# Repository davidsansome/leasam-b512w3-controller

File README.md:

# Leasam B512W3 aircon wall controller — reverse engineering and replacement

This repo documents how a **Leasam Controls B512W3** wall pad talks to its outdoor relay module, and replaces it with an ESP32 board (controlled from Home Assistant) plus a repurposed Kindle as a touchscreen wall controller.

## Safety

> **⚠️ Use at your own risk.**
>
> - This project reverse-engineers and replaces part of the control electronics for a **mains-powered air conditioner / heat pump**. Getting it wrong can damage the unit, create a shock or fire hazard, or trip breakers in ways that aren't obvious from outside.
> - None of this is reviewed, endorsed, or supported by Leasam, your HVAC manufacturer, or your installer. It is **not a certified replacement part**.
> - It may **void your warranty**, your insurance, or breach local electrical regulations in your area — check before you start.
> - If you are not confident working inside a powered appliance, get a licensed electrician or HVAC technician to help, or to review your wiring before you connect anything.
> - Every measurement, assumption and bit of "guesswork" in these notes was true for **one specific unit**. Other Leasam models, firmware revisions, or installations may differ in ways that aren't safe to assume away.
> - **Never connect a prototype or replacement board and the original pad to the module at the same time.** Turn the aircon off at the isolator before changing any wiring.

## What's here

| | |
|---|---|
| [`leasam-b512w3-notes.md`](leasam-b512w3-notes.md) | Reverse-engineering notes on the original wall pad: how it talks to the outdoor relay module (protocol, timing, voltages), what's verified vs. guessed, and open questions. Start here. |
| [`pcb-images/`](pcb-images/) | Photos of the original pad's board, used for tracing the circuit. |
| [`scope-screenshots/`](scope-screenshots/) | Oscilloscope captures of the pad's signal, for each mode and fan speed. |
| [`replacement-board/`](replacement-board/) | The replacement: an ESP32 board that drives the relay module the way the original pad did (plus a thermostat), a second board that trickle-charges a tablet over the old in-wall cable, their firmware, and the KiCad designs. |
| [`kindle-controller/`](kindle-controller/) | A jailbroken Kindle Paperwhite, running a Rust e-ink UI, as the wall-mounted touchscreen — talking to Home Assistant, not to the relay module directly. Includes a 3D-printable wall case. |

## Suggested reading order

1. [`leasam-b512w3-notes.md`](leasam-b512w3-notes.md) — what the original pad does and how it was figured out.
2. [`replacement-board/README.md`](replacement-board/README.md) — the replacement electronics and firmware that take over that job.
3. [`replacement-board/breadboard-prototype.md`](replacement-board/breadboard-prototype.md) — a bring-up/test build using only easy-to-source parts, before committing to the PCB.
4. [`kindle-controller/README.md`](kindle-controller/README.md) — the wall-mounted touch UI.

## License

See [LICENSE](LICENSE).

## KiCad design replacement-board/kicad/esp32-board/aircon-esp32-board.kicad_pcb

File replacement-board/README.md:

# ESP32 aircon controller + tablet charger

> **⚠️ Use at your own risk.** These boards replace part of the control electronics for a mains-powered ducted air conditioner / heat pump, and connect directly to the relay module's wiring. Getting it wrong can damage the unit, create a shock or fire hazard, or void your warranty and insurance. See the [top-level README](../README.md#safety) for the full disclaimer.

Two boards replace the Leasam B512W3 wall pad:

1. **ESP32 board**, mounted near the relay module. It connects to the module's **POWER, COMMON, AUX** wires, sends the relay frames the original pad sent, and takes commands over Wi-Fi. It also feeds a switched, current-limited ~16 V output up the old in-wall cable.
2. **Tablet board**, behind the tablet at the other end of that cable. It steps the voltage down to 5 V on a current-limited USB-A socket for slow-charging an Android tablet.

| Files | |
|---|---|
| `firmware/aircon_controller/aircon_controller.ino` | ESP32 firmware, for both this board and the breadboard prototype |
| `firmware/aircon_controller/thermostat.h`, `firmware/thermostat_test/` | the thermostat's decisions, and host-side checks for them |
| `home-assistant/blueprints/aircon_rooms.yaml` | HA blueprint that gives the thermostat its rooms and their temperatures |
| `home-assistant/blueprints/tablet_charging.yaml` | HA blueprint that switches the tablet output on/off between battery thresholds |
| `kicad/esp32-board/` | KiCad project, designator map and netlist for board 1 |
| `kicad/tablet-board/` | KiCad project, designator map and netlist for board 2 |
| `case/` | 3D-printable case for board 1 |
| `../leasam-b512w3-notes.md` | reverse-engineering notes |
| `breadboard-prototype.md`, `kicad/breadboard-stage1/`, `kicad/breadboard-stage2/` | breadboard test circuit, built from common parts, for checking the module accepts our frames before fabricating |

See [`CHANGES.md`](CHANGES.md) for what changed after the 2026-11-04 design review, and why.

---

## 0. Power budget (measured)

| Measurement | Value |
|---|---|
| POWER open-circuit voltage | 19.0 V |
| Source resistance (load test: 1 kΩ / 470 Ω / 100 Ω → 18.50 / 18.11 / 15.80 V) | ≈ 20 Ω (≈ 25 Ω at light load) |
| Original pad's draw | 72 mA off, 90–100 mA running |

The design stays inside what the original pad drew:

| | Limit | Typical |
|---|---|---|
| Total draw from POWER (input limiter) | ≈ 105 mA | ~85–90 mA |
| ESP32 itself | — | ~10 mA average at ~16 V (Wi-Fi bursts come from the reservoir) |
| Tablet cable output (limiter 2) | ≈ 87 mA (80–93 mA) | ≤ ~64 mA worst case |
| Tablet USB output | ≈ 123 mA typ. at 5.07 V (R_ILIM 220k) | **≈ 0.5–0.75 W into the tablet** |

That's enough to charge a mostly-sleeping tablet slowly, and to support roughly **2 hours of screen-on time per day** on average.

The TPS2553 on the tablet board is the limit that matters in normal running. Limiter 2 sits well above the tablet board's worst-case draw, so it only acts on a short circuit. This matters because the tablet board's buck is a constant-power load: if limiter 2 ever clamped it, the input voltage would fall, the current would rise, and the board would cycle through UVLO.

---

## 1. ESP32 board

### 1.1 Block diagram

```
POWER ──┬─ R_TX 3.3Ω ── Q_TX ── GND          (TX: ~15 µs pulses)
        ├─ D_TVS SMBJ30A ── GND
        └─ D_IN ─► limiter 1 (≈105 mA) ─► VRES ─┬─► buck 3.3 V ─► ESP32-C3-WROOM-02
                                                ├─ EN divider (buck on ≈12.1 V / off ≈9.9 V)
                                                ├─ VSENSE ÷16 ─► GPIO3
                                                ├─► LP2950-5.0 ─► 5V_AUX
                                                └─► limiter 2 (≈87 mA, switched by GPIO5) ─► J_TAB ─► cable
                                                                         TAB_OUT ÷16 ─► GPIO1
AUX ──┬── R_AUX 10k ── 5V_AUX                    COMMON = GND
      └── 330k ──┬── GPIO0 (AUX_SENSE)
                100k ‖ 10 nF
                 GND
```

- **Transmitting** copies the original pad's Q2/R4: Q_TX (AO3422, R_DS(on) rated at V_GS = 2.5 V) pulls POWER to GND through 3.3 Ω. The gate is AC-coupled (C_G, R_GD), so a crashed ESP32 can't hold the line low.
- **D_IN** isolates everything behind it from the line during pulses. The module only ever sees a steady load.
- **Limiter 1** caps the total draw at about what the original pad drew.
- **Limiter 2** feeds the tablet cable. It caps the tablet's share so the ESP32 always has headroom, and protects the module if the in-wall cable is ever shorted.

### 1.2 Limiters

Both use the same two-transistor circuit. The limit is ≈ 0.65 V / R_S.

```
IN ──●── R_S ──●── node B                     Q_PASS  = BCP53-16 (PNP, SOT-223)
     │         │                              Q_SENSE = MMBT3906 (PNP, SOT-23)
  Q_SENSE E  Q_PASS E
  Q_SENSE B ───┘
  Q_SENSE C ──●── Q_PASS B ── base drive to GND
Q_PASS C ──► OUT
```

| | Limiter 1 (input) | Limiter 2 (tablet output) |
|---|---|---|
| IN → OUT | D_IN cathode → VRES | VRES → TAB_OUT |
| R_S | 6.2 Ω → ≈ 105 mA | 7.5 Ω → ≈ 87 mA |
| Base drive | R_B 10k to GND (always on) | R_B2 10k → Q_EN (MMBT3904) → GND. R_BE2 47k holds it off. |
| Switching | — | GPIO5 → R_ENB 10k → Q_EN base (R_ENBD 100k pull-down) |
| Worst-case heat | ≈ 2 W for ~0.3 s while the reservoir charges at power-up | ≈ 1.4 W into a shorted cable, until the firmware switches off (~2 s) |

Give both Q_PASS tabs a copper pour of at least 1 cm². The tab is the collector (VRES for limiter 1, TAB_OUT for limiter 2).

On the tablet output there's also D_TVS2 (SMBJ24A), C_TAB 100 nF, and a ÷16 sense divider (150k/10k, 100 nF) to GPIO1.

### 1.3 Reservoir, 3.3 V buck, ESP32

- **Reservoir:** 2× 1000 µF 63 V plus 2.2 µF 50 V X7R.
- **Buck enable divider:** 1M / 113k (on ≈ 12.1 V, off ≈ 9.9 V).
- **VSENSE:** 150k / 10k ÷16 to GPIO3.
- **Buck:** LMR51606YDBVR (1.1 MHz PFM) with 10 µH, 69.8k / 22.1k feedback (3.33 V), and 2× 22 µF + 100 µF out.

ESP32-C3-WROOM-02 pins:

| Pin | Signal | Connection |
|---|---|---|
| 1 | 3V3 | 3V3, 10 µF + 100 nF |
| 2 | EN | 10k to 3V3, 1 µF to GND, J_PROG |
| 3 | IO4 | TX gate drive (R_G 47 Ω → C_G 100 nF → Q_TX gate) |
| 4 | IO5 | tablet output enable |
| 7 / 16 | IO8 / IO2 | 10k pull-ups (strapping) |
| 8 | IO9 | BOOT → J_PROG |
| 10 | IO10 | LED via 1k |
| 11 / 12 | RXD0 / TXD0 | J_PROG |
| 5 / 6 / 13 / 14 | IO6 / IO7 / IO18 / IO19 | not connected |
| 15 | IO3 | VSENSE |
| 18 | IO0 | AUX_SENSE (AUX ÷4.3: 330k / 100k, 10 nF) |
| 17 | IO1 | tablet output sense |
| 9, 19 | GND | GND (19 is the centre pad) |

### 1.4 Connectors

| Ref | Pins |
|---|---|
| J_MOD (3-way 5.08 mm screw terminal) | 1 POWER, 2 COMMON, 3 AUX: short wires to the relay module |
| J_TAB (2-way 5.08 mm screw terminal) | 1 OUT+, 2 GND: to the in-wall cable |
| J_PROG (1×6 header) | 1 3V3, 2 GND, 3 EN, 4 IO9, 5 RXD0, 6 TXD0. The only wired way to flash the board (see below). |
| AUX | Always loaded with R_AUX 10k to 5V_AUX, the same as the original pad (R66 10k to its 5 V rail). Read on GPIO0. |

**Flashing.** After the first flash, update over Wi-Fi (OTA). For the first flash, or to recover from an OTA update that broke Wi-Fi, use a 3.3 V USB-UART adapter on J_PROG:

- Connect adapter GND → pin 2, TX → pin 5 (RXD0), RX → pin 6 (TXD0).
- Power the board from J_MOD or a bench supply, not from the adapter. Leave pin 1 (3V3) unconnected: most adapters can't supply the ESP32's Wi-Fi bursts, and it would back-feed the buck's output.
- To enter the bootloader: hold pin 4 (IO9) to GND, briefly short pin 3 (EN) to GND, then release IO9. The board has no auto-reset circuit, so an adapter's DTR/RTS lines won't do this.

---

## 2. Tablet board

```
J_IN+ ──┬─ D_TVS SMBJ24A ── GND
        └─ D_REV SS16 ─► VIN ─┬─ C_BULK 100µF 35V, C_IN 2.2µF 50V
                              ├─ UVLO divider 1M / 150k → EN (on ≈ 9.4 V, off ≈ 7.6 V)
                              └─ LMR51606 buck ─► 5 V (160k / 30k → 5.07 V, 10 µH, 2× 10 µF 50 V)
                                                   └─► TPS2553 current-limit switch ─► VBUS ─► USB-A
                                                       R_ILIM 220k → ≈ 123 mA typ.
```

- **D_TVS before D_REV:** if the cable is wired backwards, the TVS conducts and the ESP32 board's limiter 2 holds the current at ~87 mA until the firmware's fault detection switches it off. Nothing gets damaged.
- **TPS2553 (not the -1 version):** in overload it holds a constant current rather than latching off. A tablet asking for 1–2 A just sees VBUS sag slightly, and its charger backs off. Without this, the tablet would pull the input down, the buck would cut out and restart, and the tablet would see the charger repeatedly connecting and disconnecting.
- **The output limit is set well below what the cable can supply.** At worst case (≈ 0.74 W out, ≈ 85% buck efficiency, ~13.5 V at the board) the board draws ≈ 64 mA, against limiter 2's minimum of ≈ 79 mA after base drive. That margin is what stops the input collapsing.
- **Data lines:** left open by default, which tablets treat as a basic USB port. JP_DCP shorts D+ and D− (a "dedicated charger") if your tablet charges better that way. The limit is the same either way.
- **USB connection:** use a normal USB-A to USB-C cable to the tablet. The cable handles the USB-C side.

---

## 3. Firmware

One sketch, [`firmware/aircon_controller/`](firmware/aircon_controller/), serves both this board and the breadboard prototype. The board is picked from the chip it's compiled for: ESP32-C3 (`esp32:esp32:esp32c3`) builds for this board, and a classic ESP32 (`esp32:esp32:esp32`) builds for the breadboard. It needs the PubSubClient library. Copy `secrets.example.h` to `secrets.h` (git ignores it) and fill in the Wi-Fi, MQTT broker and OTA password.

It's controlled from Home Assistant over MQTT discovery, as an **Aircon** device: Power, Mode (Cool / Heat / Fan only / Auto), Fan speed, a Compressor running sensor, a No flow problem sensor (see [flow interlock](#flow-interlock)), the [thermostat](#thermostat), and diagnostics. It also handles RMT frame timing, the compressor lockout, OTA (host `aircon`), Wi-Fi recovery and a loop watchdog. See the comment at the top of the sketch for the details.

Before starting Wi-Fi, it waits up to 20 s for VRES to reach 13 V, so the reservoir is charged before Wi-Fi's current bursts. "VRES at boot" and "Boot Wi-Fi wait" report how that went.

The **tablet output manager** is configurable at the top of the sketch.

| Rule | Default |
|---|---|
| Stays off for the first 30 s after boot | `TAB_BOOT_DELAY_MS` |
| Switches on when VRES ≥ 14 V for 10 s | `TAB_ON_MIN_V`, `TAB_ON_SETTLE_MS` |
| **Load shedding:** off if VRES < 13 V for 0.5 s | `TAB_SHED_V` |
| **Fault:** off if output < 10 V for 2 s while on (shorted cable, reversed wiring) | `TAB_FAULT_V` |
| Retry after a shed or fault | 60 s |

The Home Assistant entities for the tablet output:
- **Tablet output:** a switch that enables or disables the output. Turning it on also clears a pending retry wait. It isn't saved, so it is on again after every reboot.
- **Tablet output status:** text, such as "On", "Waiting: VRES settling", "Shed: VRES low" or "Fault: output low".
- **Tablet output voltage:** the 10 s mean.
- **Tablet output sheds** and **Tablet output faults:** counts since boot.

**Automated charging limits:** to avoid holding a wall-mounted Li-Po battery at 100% continuously, use the *Tablet charging* blueprint, [`home-assistant/blueprints/tablet_charging.yaml`](home-assistant/blueprints/tablet_charging.yaml) (needs HA 2024.10 or later). It switches **Tablet output** on when the battery sensor drops to or below the low threshold, and off at or above the high threshold. It also re-checks on HA startup, every 10 minutes, and whenever **Tablet output** changes state (so an ESP32 reboot, which resets the output to on, won't charge past the high threshold). If the battery sensor is unavailable or stops reporting, it fails safe and turns **Tablet output** back on within about 10 minutes of the stale timeout (default 30 min; keep this at least 3× the Kindle's `diagnostics_interval_secs`, which defaults to 5 min) so the wall panel can't drain to empty unattended.

- **Suggested thresholds for the Kindle Paperwhite 10th gen:** **40%–75%** (the blueprint's defaults; up to **80%** if you want a bit more outage reserve). Stopping at 75–80% reduces Li-Po calendar aging and swelling risk, while starting at 40% leaves plenty of buffer for the tablet board's slow ~+50 mA net charge rate (~3%/hr).
- **Manual overrides & outages:** disable the automation if you want to override **Tablet output** manually outside the configured band. Note also that the ESP32 itself keeps its last `Tablet output` state while HA/MQTT is unreachable, so a prolonged HA outage while the output is off won't resume charging until HA returns or the ESP32 reboots.
- **To add it:** copy `tablet_charging.yaml` to `config/blueprints/automation/aircon/` in HA (or import its raw URL under *Settings → Automations & scenes → Blueprints → Import blueprint*), reload automations, and create an automation picking the Kindle's **Battery level** sensor and the Aircon's **Tablet output** switch.

AUX, VRES and the tablet output are sampled at ~1 kHz. Every 10 s the firmware publishes the mean, plus the lowest and highest single sample (AUX minimum/maximum, VRES minimum), so short dips and spikes still show up. Home Assistant's history serves as the AUX log, for spotting rare events such as a defrost or a fault. The AUX ratio on this board hasn't been calibrated against a meter yet.

### Flow interlock

AUX reports the building's condenser-water flow interlock. Once the central pump's flow switch proves flow, the interlock puts +24 V on the unit's VERIFY wire, and the relay module raises AUX: the firmware reported a steady 1.31 V with flow proven (whether off, fan only or cooling) and 0.56 V with VERIFY disconnected (minimum and maximum both 0.56 V). The original pad shows "E-C" when the building pump stops, so E-C is its no-flow error. The module itself still lets the compressor start without VERIFY (the original pad was presumably the interlock), and a water-loop compressor run without flow risks high head pressure, so the firmware does it:

- **No flow** is a 1 s AUX mean below 0.90 V (`NO_FLOW_BELOW_V`); flow is OK again above 1.00 V (`FLOW_OK_ABOVE_V`). Either state must hold for 5 s (`FLOW_DEBOUNCE_MS`) before it counts, so mains hum and brief dips don't trip it.
- With no flow the whole unit idles: no compressor and no fan. A running compressor stops at once, even inside the minimum run time. Power, Mode and Fan speed keep their values. **Operation** reads `No flow` whenever the unit would otherwise run.
- Once flow is back the unit resumes, fan first; the 3-minute lockout from when the compressor stopped still applies.
- After boot there's taken to be no flow until AUX has read OK for 5 s (the 3-minute boot lockout covers that anyway). No flow isn't published during that check, so a reboot doesn't flash the error on the wall controller; it's reported only once AUX has actually stayed low for 5 s.
- **No flow** (`binary_sensor.aircon_no_flow`, a problem sensor) is on with no flow. The Kindle controller reads it. Changes are also logged to Serial (115200 baud).

The thresholds are the same for both builds, set from the figures above. The PCB's AUX ratio isn't calibrated, so check its reported AUX with and without flow before relying on it there.

A rising shed count means the tablet's draw is pushing the budget. Lower R_ILIM's current (raise R_ILIM) or check VRES. A fault count means something is wrong on the cable side.

The firmware compiles for both chips (Arduino-ESP32 3.3.12). Apart from the 1 kHz sampling and the thermostat, the breadboard build is the sketch that was tested on the breadboard. The PCB-only parts (tablet output, VRES wait, pins and dividers) haven't run on a board yet.

### Thermostat

With **Thermostat** on and the mode Cool or Heat, the controller switches the whole unit off ("idle") when the room temperature reaches the **Set point**, and back on once it's **Thermostat hysteresis** beyond it (above the set point when cooling, below it when heating). Power, Mode and Fan speed keep their values throughout. **Operation** shows what the unit is really doing: `Off`, `Heating`, `Cooling`, `Fan` (fan only, or the fan running while the compressor lockout holds the compressor off) or `No flow` (the [flow interlock](#flow-interlock) holds the whole unit idle). With Thermostat off (continuous) the unit runs whatever the temperature, and in Fan only mode the thermostat has no effect.

**Auto** heats or cools as needed, around one set point. It works like Heat with a set point of *Set point − Auto deadband*, or like Cool with *Set point + Auto deadband* (deadband 0.5–5 °C, default 1). With a set point of 22 °C, a 1 °C deadband and 0.5 °C hysteresis, it cools from 23.5 °C down to 23 °C, and heats from 20.5 °C up to 21 °C; in between it idles. On entering Auto (or switching the power on) it starts in the direction of the side of the set point the temperature is on. It changes direction only once the temperature is past the other direction's resume point (20.5 °C or 23.5 °C here), so it can't flip between heating and cooling near the set point. A change of direction stops the compressor, and the 3-minute lockout applies before it starts the other way. **Auto direction** shows `Heat` or `Cool` (unknown outside Auto, or before there's a temperature). Auto needs the thermostat: with Thermostat off (continuous), the unit stays idle.

- **Which temperature:** **Thermostat room** is `Average` (every room with a fresh reading) or one room's name. **Thermostat temperature** shows the value in use.
- **Short cycles:** once the compressor starts, it runs for at least **Minimum run time** (default 3 min) before the thermostat may stop it. The 3-minute compressor lockout still applies when it restarts, so the fan comes on first.
- **No temperature:** with no usable reading, the unit stays idle. A reading is unusable if the sensor is unavailable, if it's over 5 minutes old (`ROOM_STALE_MS`), or while HA is offline (`homeassistant/status`). This also covers HA going down: you couldn't switch the unit off then, so it doesn't run unattended.
- **Thermostat status** says which of these applies: `Off`, `Continuous`, `Fan only`, `Running`, `Running: minimum run time`, `Idle: at set point`, `Idle: near set point` (Auto, between heating and cooling), `Idle: no temperature`, `Idle: no rooms configured` or `Idle: Auto needs the thermostat`.
- Set point (16–30 °C), hysteresis (0.1–3 °C, default 0.5), Auto deadband, minimum run time (0–30 min), the Thermostat switch, the room selection and the room list are kept over a reboot.

**Rooms** are set up in Home Assistant with the *Aircon rooms* blueprint, [`home-assistant/blueprints/aircon_rooms.yaml`](home-assistant/blueprints/aircon_rooms.yaml). Its form has a picker for the Aircon device and up to four rooms, each a temperature sensor (filtered to temperature sensors) and an optional name; the name defaults to the sensor's area. The automation publishes each room's name and sensor (retained) and its temperature (converted from °F if needed) to `<node>/room/<1-4>/…`, whenever a sensor changes and every minute. The controller lists the rooms in its **Rooms** entity's attributes, which is where the Kindle controller reads them from.

To add the blueprint (needs HA 2024.10 or later):

1. Copy `aircon_rooms.yaml` to `config/blueprints/automation/aircon/` in HA, then *Developer tools → YAML → Reload automations*. Once this repo is reachable online, *Settings → Automations & scenes → Blueprints → Import blueprint* with the file's raw URL does the same, and lets HA re-import newer versions.
2. On the blueprint, choose *Create automation*, pick the Aircon device and the rooms, and save. Change rooms there later.

Without it, Thermostat status reads `Idle: no rooms configured`, and Continuous mode still works.

`firmware/thermostat_test/thermostat_test.cpp` checks the thermostat's decisions on a PC: `g++ -std=c++17 -Wall -o thermostat_test thermostat_test.cpp && ./thermostat_test`.

---

## 4. Bring-up

1. **ESP32 board alone, on the bench.** Feed J_MOD through ~20 Ω from a 19 V supply to imitate the module. Check:
   - VRES charges and the buck starts.
   - Wi-Fi connects.
   - The pulses on the scope match the original captures.
2. **Tablet output.** Connect a 220 Ω 2 W resistor to J_TAB. After ~40 s, Home Assistant should show Tablet output status "On", with Tablet output voltage ≈ 15–16 V and roughly 70 mA flowing. Short J_TAB briefly: within ~2 s the status should change to a fault and the output switch off.
3. **Tablet board, on the bench.** Feed it from the ESP32 board's J_TAB, then:
   - with no load, check ≈ 5.07 V at USB
   - with a USB load tester, check the current limit settles at ~123 mA and the ESP32 board's VRES stays above 15 V
4. **Install.** Connect the ESP32 board at the module and the tablet board at the wall. Check that VRES minimum and Tablet output sheds stay healthy over a day.

---

## 5. Assumptions (not verified)

- **Running current is assumed to be ~100 mA.** The meter reading while running was disturbed by the meter itself. A measurement through a 1 Ω resistor would confirm it.
- **The module is assumed to tolerate ~90–105 mA continuously,** as it did with the original pad.
- **Frame meaning and timing:** see the notes file. Bits 2/3 are unknown, and timings are ±0.2 ms from screenshots.
- **Charging behaviour varies by tablet.** Most Android tablets reduce their charge current when VBUS sags, but check yours on the bench (step 3). The Kindle Paperwhite 10th gen doesn't:
  - With JP1 open it sees a computer port that never sets it up as a USB device, and doesn't charge. **Close JP1** so it sees a dedicated charger.
  - Even then, its charger's adaptive input limit trips on the TPS2553's limit and suspends. The Kindle controller detects this and sets a fixed 100 mA input limit (see `kindle-controller/src/charge_guard.rs`). Measured on the bench: about +50 mA into the battery, with VBUS at 5.0 V.
- **Part pinouts:** check Q_TX (1 G, 2 S, 3 D), BCP53 (1 B, 2 C, 3 E, tab C) and the LP2950CDT (1 IN, 2/tab GND, 3 OUT) against the actual parts you buy.
- **LP2950 output capacitor:** some LP2950 makes need a tantalum or a minimum ESR on the output. Check the datasheet of the brand you buy against C_5V (2.2 µF ceramic).
- **AUX:** the module side loads AUX with roughly 15k (it sits at ~3 V with the original pad). It reports the condenser-water flow interlock (VERIFY), and the firmware acts on it: see [Flow interlock](#flow-interlock). Whether it carries anything else (a fault, a defrost) is still unknown.

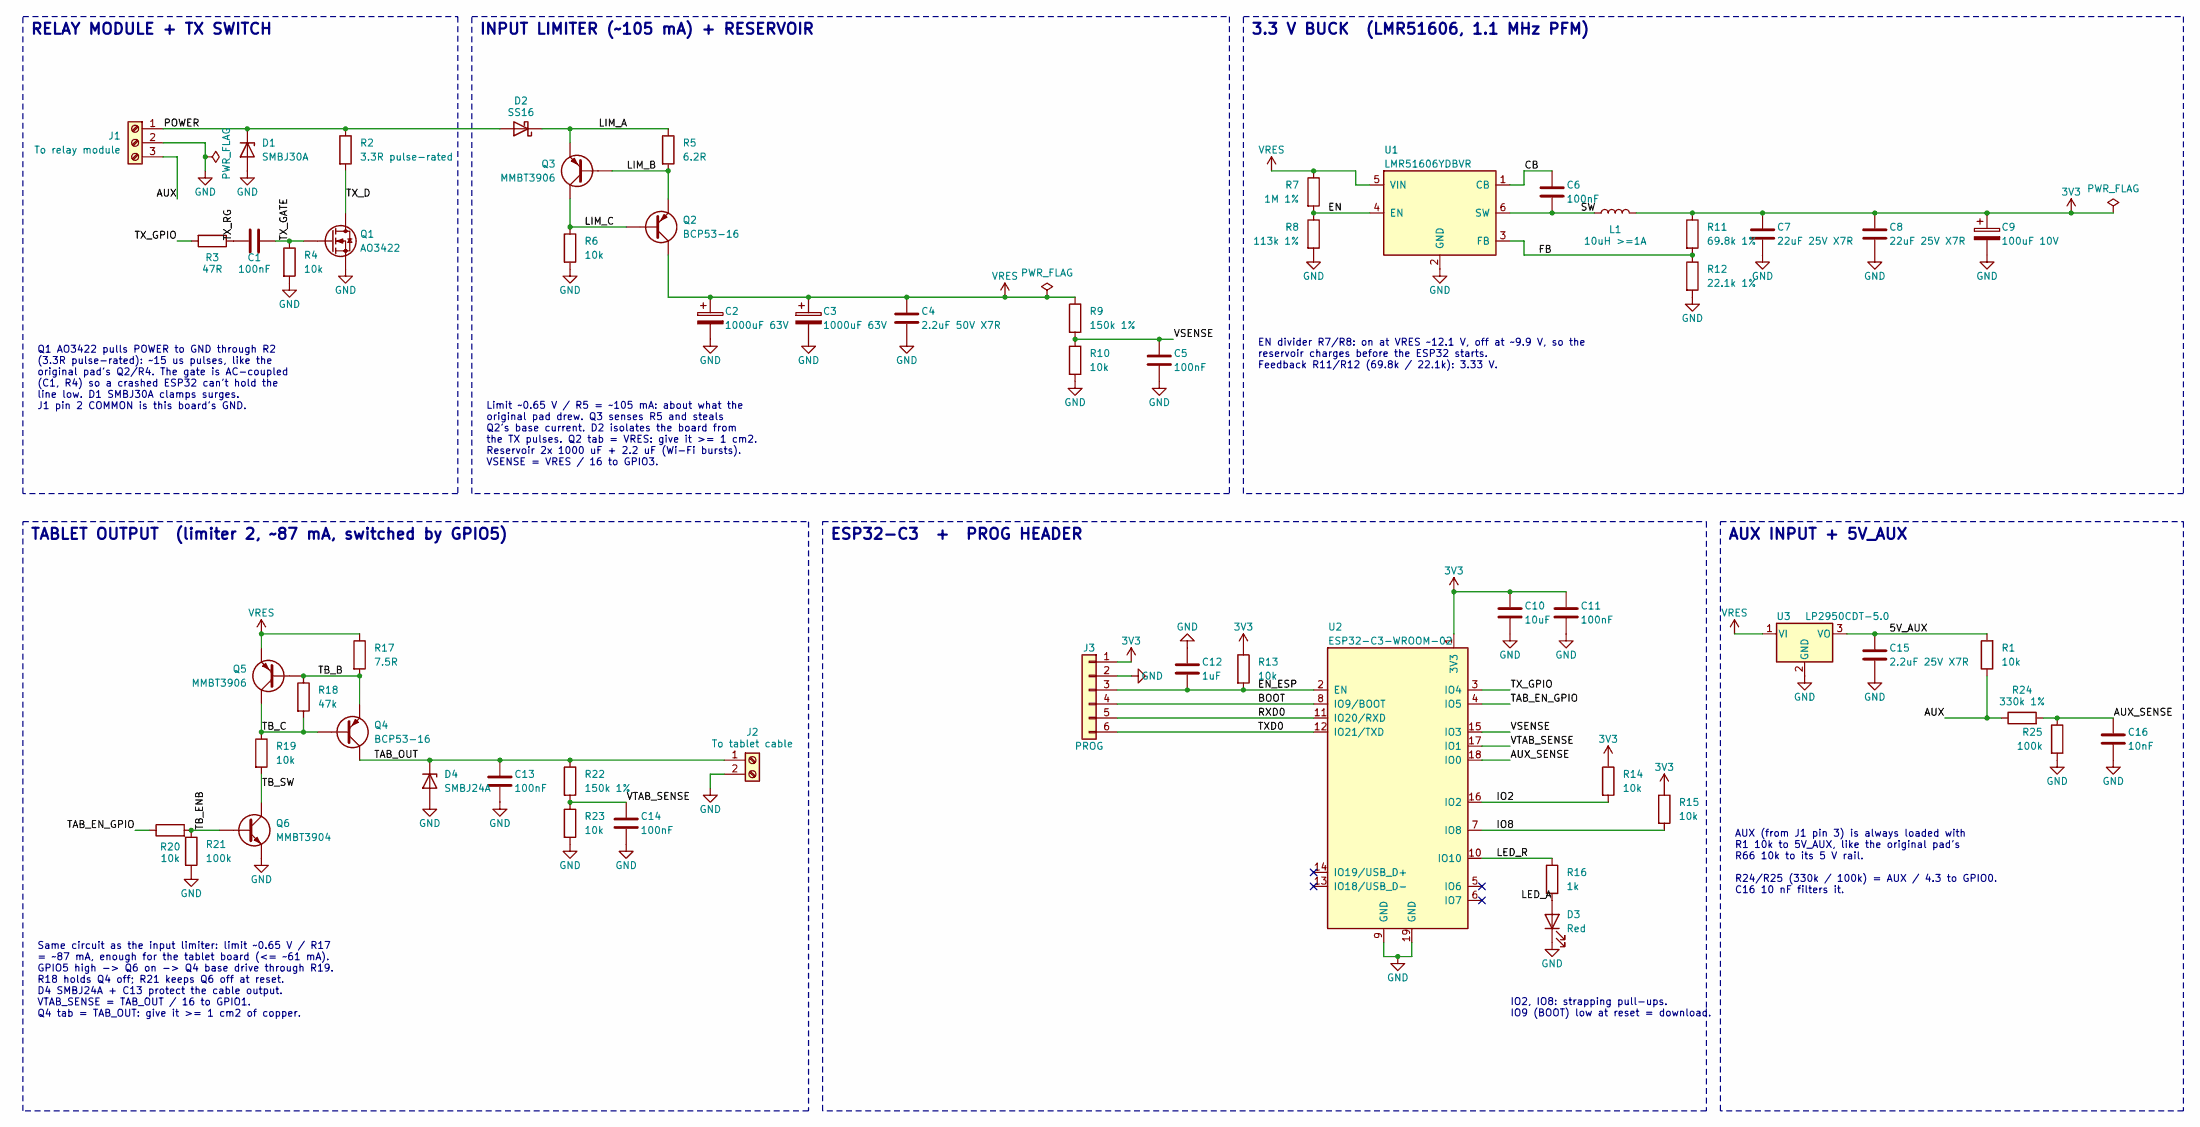
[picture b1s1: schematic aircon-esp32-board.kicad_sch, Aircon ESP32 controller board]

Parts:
C1, C5, C6, C11, C13, C14: 100nF; C_0603_1608Metric; JLCPCB Part # C1591
C2, C3: 1000uF 63V; CP_Radial_D16.0mm_P7.50mm; JLCPCB Part # C10744
C4: 2.2uF 50V X7R; C_1206_3216Metric; JLCPCB Part # C50254
C7, C8: 22uF 25V X7R; C_0805_2012Metric; JLCPCB Part # C45783
C9: 100uF 10V; CP_EIA-3528-21_Kemet-B; JLCPCB Part # C600583
C10: 10uF; C_0805_2012Metric; JLCPCB Part # C15850
C12: 1uF; C_0603_1608Metric; JLCPCB Part # C29936
C15: 2.2uF 25V X7R; C_0805_2012Metric; JLCPCB Part # C380349
C16: 10nF; C_0603_1608Metric; JLCPCB Part # C1589
D1: SMBJ30A; D_SMB; JLCPCB Part # C86181
D2: SS16; D_SMA; JLCPCB Part # C2481
D3: Red; LED_0603_1608Metric; JLCPCB Part # C2286
D4: SMBJ24A; D_SMB; JLCPCB Part # C5178956
J1: To relay module; TerminalBlock_Phoenix_MKDS-1,5-3-5.08_1x03_P5.08mm_Horizont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; JLCPCB Part # C474953
J2: To tablet cable; TerminalBlock_Phoenix_MKDS-1,5-2-5.08_1x02_P5.08mm_Horizont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; JLCPCB Part # C474952
J3: PROG; PinHeader_1x06_P2.54mm_Vertical; JLCPCB Part # C40877
L1: 10uH >=1A; L_Bourns-SRN4018; JLCPCB Part # C503307
Q1: AO3422; SOT-23; JLCPCB Part # C37130
Q2, Q4: BCP53-16; SOT-223-3_TabPin2; JLCPCB Part # C148109
Q3, Q5: MMBT3906; SOT-23; JLCPCB Part # C53444
Q6: MMBT3904; SOT-23; JLCPCB Part # C20526
R1, R4, R6, R10, R13, R14, R15, R19, R20, R23: 10k; R_0603_1608Metric; JLCPCB Part # C25804
R2: 3.3R pulse-rated; R_1206_3216Metric; JLCPCB Part # C2074853
R3: 47R; R_0603_1608Metric; JLCPCB Part # C23182
R5: 6.2R; R_0805_2012Metric; JLCPCB Part # C6040134
R7: 1M 1%; R_0603_1608Metric; JLCPCB Part # C22935
R8: 113k 1%; R_0603_1608Metric; JLCPCB Part # C22862
R9, R22: 150k 1%; R_0603_1608Metric; JLCPCB Part # C22807
R11: 69.8k 1%; R_0603_1608Metric; JLCPCB Part # C23098
R12: 22.1k 1%; R_0603_1608Metric; JLCPCB Part # C25961
R16: 1k; R_0603_1608Metric; JLCPCB Part # C21190
R17: 7.5R; R_0805_2012Metric; JLCPCB Part # C873769
R18: 47k; R_0603_1608Metric; JLCPCB Part # C25819
R21, R25: 100k; R_0603_1608Metric; JLCPCB Part # C25803
R24: 330k 1%; R_0603_1608Metric; JLCPCB Part # C23137
U1: LMR51606YDBVR; SOT-23-6; JLCPCB Part # C33545953
U2: ESP32-C3-WROOM-02; JLCPCB Part # C2934560
U3: LP2950CDT-5.0; TO-252-2; JLCPCB Part # C179571

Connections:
3V3: C7.1, C8.1, C9.1, C10.1, C11.1, J3.1, L1.2, R11.1, R13.1, R14.1, R15.1, U2.1 (3V3)
/5V_AUX: C15.1, R1.2, U3.3 (VO)
/AUX: J1.3, R1.1, R24.1
/AUX_SENSE: C16.1, R24.2, R25.1, U2.18 (IO0)
/BOOT: J3.4, U2.8 (IO9/BOOT)
/CB: C6.1, U1.1 (CB)
/EN: R7.2, R8.1, U1.4 (EN)
/EN_ESP: C12.1, J3.3, R13.2, U2.2 (EN)
/FB: R11.2, R12.1, U1.3 (FB)
/IO2: R14.2, U2.16 (IO2)
/IO8: R15.2, U2.7 (IO8)
/LED_A: D3.2 (A), R16.2
/LED_R: R16.1, U2.10 (IO10)
/LIM_A: D2.1 (K), Q3.2 (E), R5.1
/LIM_B: Q2.3 (E), Q3.1 (B), R5.2
/LIM_C: Q2.1 (B), Q3.3 (C), R6.1
/POWER: D1.1 (K), D2.2 (A), J1.1, R2.1
/RXD0: J3.5, U2.11 (IO20/RXD)
/SW: C6.2, L1.1, U1.6 (SW)
/TAB_EN_GPIO: R20.1, U2.4 (IO5)
/TAB_OUT: C13.1, D4.1 (K), J2.1, Q4.2 (C), R22.1
/TB_B: Q4.3 (E), Q5.1 (B), R17.2, R18.1
/TB_C: Q4.1 (B), Q5.3 (C), R18.2, R19.1
/TB_ENB: Q6.1 (B), R20.2, R21.1
/TB_SW: Q6.3 (C), R19.2
/TXD0: J3.6, U2.12 (IO21/TXD)
/TX_D: Q1.3 (D), R2.2
/TX_GATE: C1.1, Q1.1 (G), R4.1
/TX_GPIO: R3.2, U2.3 (IO4)
/TX_RG: C1.2, R3.1
/VSENSE: C5.1, R9.2, R10.1, U2.15 (IO3)
/VTAB_SENSE: C14.1, R22.2, R23.1, U2.17 (IO1)
GND: C2.2, C3.2, C4.2, C5.2, C7.2, C8.2, C9.2, C10.2, C11.2, C12.2, C13.2, C14.2, C15.2, C16.2, D1.2 (A), D3.1 (K), D4.2 (A), J1.2, J2.2, J3.2, Q1.2 (S), Q6.2 (E), R4.2, R6.2, R8.2, R10.2, R12.2, R21.2, R23.2, R25.2, U1.2 (GND), U2.9 (GND), U2.19 (GND), U3.2 (GND)
VRES: C2.1, C3.1, C4.1, Q2.2 (C), Q5.2 (E), R7.1, R9.1, R17.1, U1.5 (VIN), U3.1 (VI)

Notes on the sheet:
Same circuit as the input limiter: limit ~0.65 V / R17 = ~87 mA, enough for the tablet board (<= ~61 mA). GPIO5 high -> Q6 on -> Q4 base drive through R19. R18 holds Q4 off; R21 keeps Q6 off at reset. D4 SMBJ24A + C13 protect the cable output. VTAB_SENSE = TAB_OUT / 16 to GPIO1. Q4 tab = TAB_OUT: g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
ESP32-C3 + PROG HEADER
RELAY MODULE + TX SWITCH
3.3 V BUCK (LMR51606, 1.1 MHz PFM)
Q1 AO3422 pulls POWER to GND through R2 (3.3R pulse-rated): ~15 us pulses, like the original pad's Q2/R4. The gate is AC-coupled (C1, R4) so a crashed ESP32 can't hold the line low. D1 SMBJ30A clamps surges. J1 pin 2 COMMON is this board's GND.
AUX INPUT + 5V_AUX
IO2, IO8: strapping pull-ups. IO9 (BOOT) low at reset = download.
INPUT LIMITER (~105 mA) + RESERVOIR
EN divider R7/R8: on at VRES ~12.1 V, off at ~9.9 V, so the reservoir charges before the ESP32 starts. Feedback R11/R12 (69.8k / 22.1k): 3.33 V.
AUX (from J1 pin 3) is always loaded with R1 10k to 5V_AUX, like the original pad's R66 10k to its 5 V rail. R24/R25 (330k / 100k) = AUX / 4.3 to GPIO0. C16 10 nF filters it.
Limit ~0.65 V / R5 = ~105 mA: about what the original pad drew. Q3 senses R5 and steals Q2's base current. D2 isolates the board from the TX pulses. Q2 tab = VRES: give it >= 1 cm2. Reservoir 2x 1000 uF + 2.2 uF (Wi-Fi bursts). VSENSE = VRES / 16 to GPIO3.
TABLET OUTPUT (limiter 2, ~87 mA, switched by GPIO5)

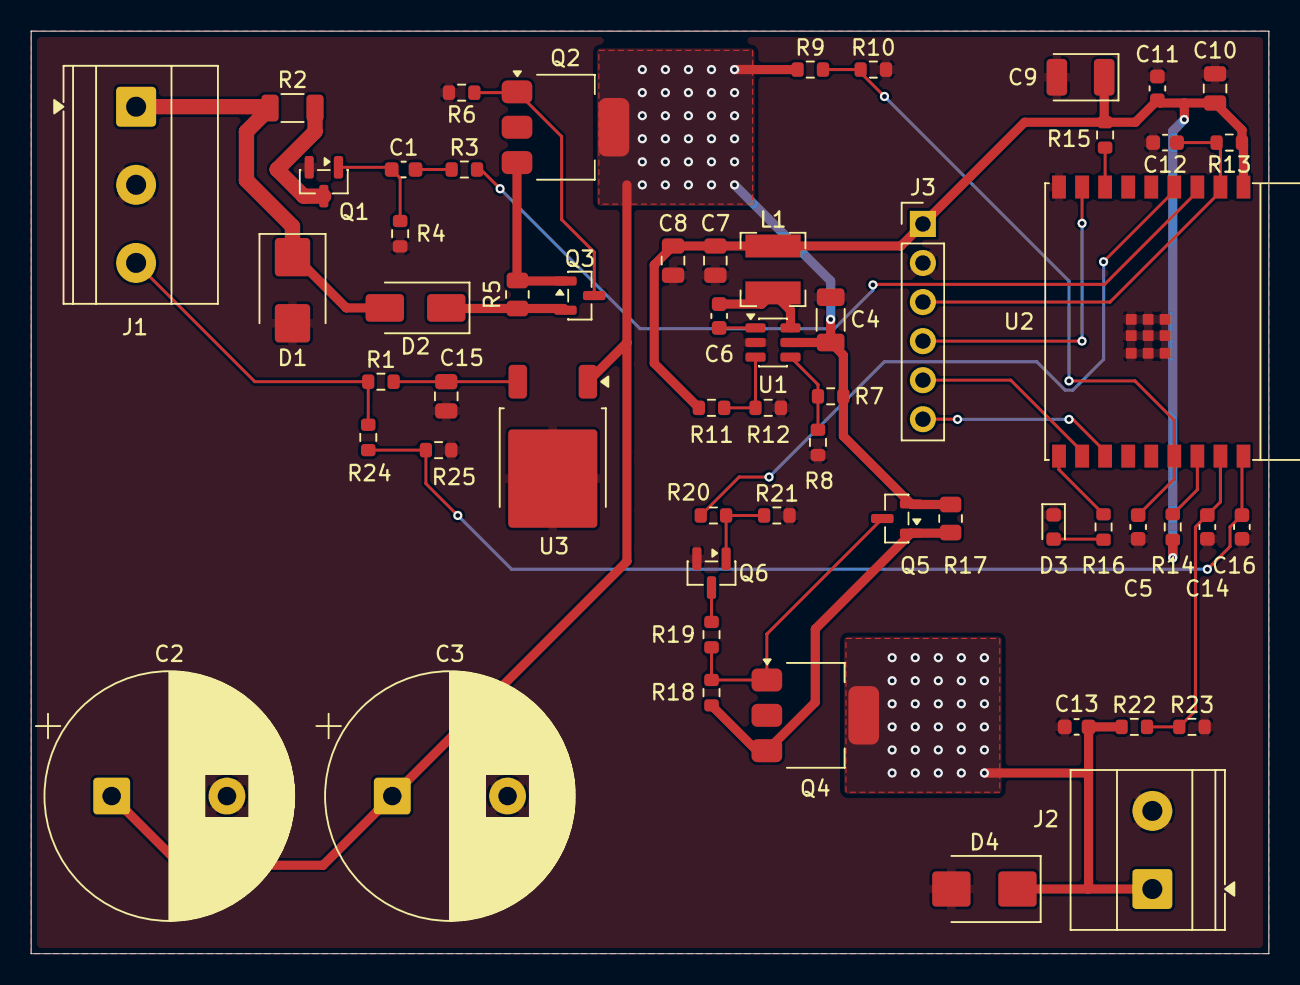
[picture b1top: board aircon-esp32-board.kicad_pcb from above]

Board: 2 copper layers, 80.5 x 60.0 mm, 58 parts (0 on the bottom side), 34 nets.

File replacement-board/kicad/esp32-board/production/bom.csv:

Designator,Footprint,Quantity,Value,LCSC Part #
"C1, C11, C13, C14, C5, C6",0603,6,100nF,C1591
C10,0805,1,10uF,C15850
C12,0603,1,1uF,C29936
C15,0805,1,2.2uF 25V X7R,C380349
C16,0603,1,10nF,C1589
"C2, C3",CP_Radial_D16.0mm_P7.50mm,2,1000uF 63V,C10744
C4,1206,1,2.2uF 50V X7R,C50254
"C7, C8",0805,2,22uF 25V X7R,C45783
C9,CP_EIA-3528-21_Kemet-B,1,100uF 10V,C600583
D1,D_SMB,1,SMBJ30A,C86181
D2,D_SMA,1,SS16,C2481
D3,0603,1,Red,C2286
D4,D_SMB,1,SMBJ24A,C5178956
J1,"TerminalBlock_Phoenix_MKDS-1,5-3-5.08_1x03_P5.08mm_Horizontal",1,To relay module,C474953
J2,"TerminalBlock_Phoenix_MKDS-1,5-2-5.08_1x02_P5.08mm_Horizontal",1,To tablet cable,C474952
J3,PinHeader_1x06_P2.54mm_Vertical,1,PROG,C40877
L1,L_Bourns-SRN4018,1,10uH >=1A,C503307
Q1,SOT-23,1,AO3422,C37130
"Q2, Q4",SOT-223-3_TabPin2,2,BCP53-16,C148109
"Q3, Q5",SOT-23,2,MMBT3906,C53444
Q6,SOT-23,1,MMBT3904,C20526
"R1, R10, R13, R14, R15, R19, R20, R23, R4, R6",0603,10,10k,C25804
R11,0603,1,69.8k 1%,C23098
R12,0603,1,22.1k 1%,C25961
R16,0603,1,1k,C21190
R17,0805,1,7.5R,C873769
R18,0603,1,47k,C25819
R2,1206,1,3.3R pulse-rated,C2074853
"R21, R25",0603,2,100k,C25803
"R22, R9",0603,2,150k 1%,C22807
R24,0603,1,330k 1%,C23137
R3,0603,1,47R,C23182
R5,0805,1,6.2R,C6040134
R7,0603,1,1M 1%,C22935
R8,0603,1,113k 1%,C22862
U1,SOT-23-6,1,LMR51606YDBVR,C33545953
U2,ESP32-C3-WROOM-02,1,ESP32-C3-WROOM-02,C2934560
U3,TO-252-2,1,LP2950CDT-5.0,C179571

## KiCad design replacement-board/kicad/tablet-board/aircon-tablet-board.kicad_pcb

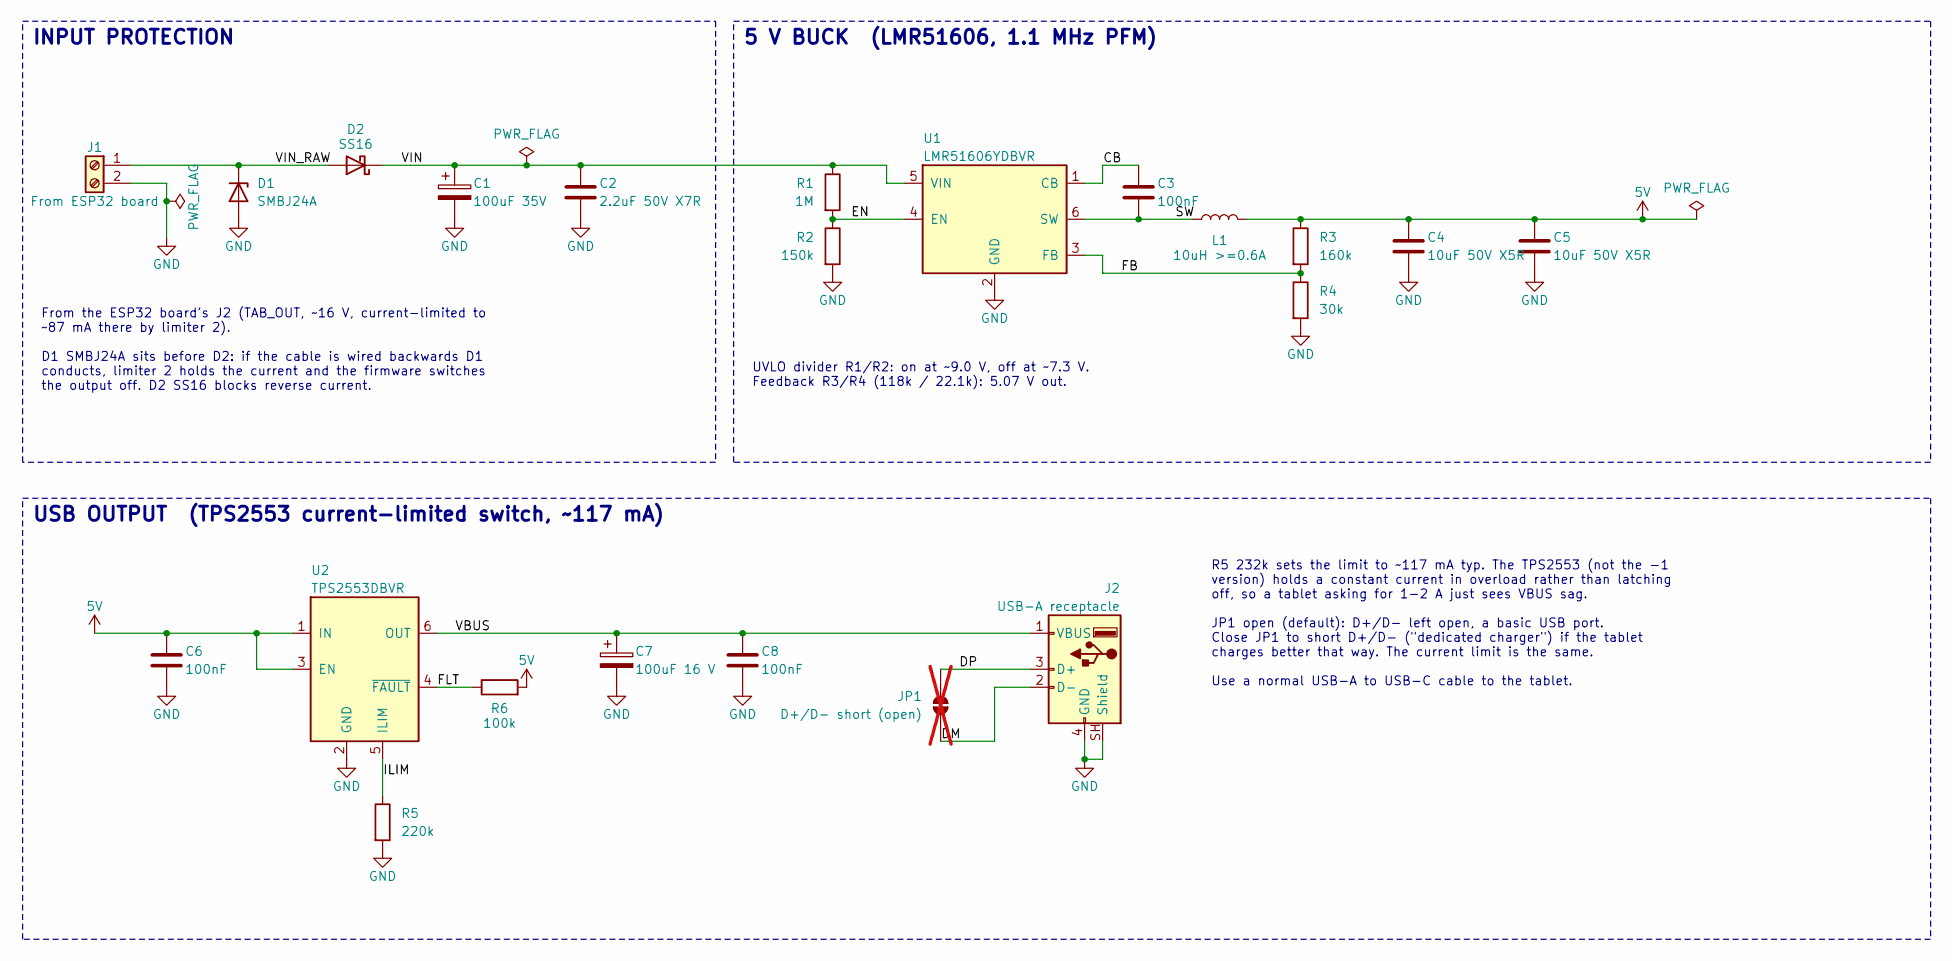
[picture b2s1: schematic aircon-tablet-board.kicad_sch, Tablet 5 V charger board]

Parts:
C1: 100uF 35V; CP_Elec_6.3x7.7; LCSC Part # C2992597
C2: 2.2uF 50V X7R; C_1206_3216Metric; LCSC Part # C50254
C3, C6, C8: 100nF; C_0603_1608Metric; LCSC Part # C1591
C4, C5: 10uF 50V X5R; C_1206_3216Metric; LCSC Part # C13585
C7: 100uF 16 V; CP_Radial_D6.3mm_P2.50mm; LCSC Part # C55265386
D1: SMBJ24A; D_SMB; LCSC Part # C5178956
D2: SS16; D_SMA; LCSC Part # C2481
J1: From ESP32 board; TerminalBlock_Phoenix_MKDS-1,5-2-5.08_1x02_P5.08mm_Horizont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; LCSC Part # C474952
J2: USB-A receptacle; USB_A_Molex_67643_Horizontal; LCSC Part # C293351
JP1: D+/D- short (open); SolderJumper-2_P1.3mm_Open_RoundedPad1.0x1.5mm; not fitted
L1: 10uH >=0.6A; L_Bourns-SRN4018; LCSC Part # C503307
R1: 1M; R_0603_1608Metric; LCSC Part # C22935
R2: 150k; R_0603_1608Metric; LCSC Part # C22807
R3: 160k; R_0603_1608Metric; LCSC Part # C2930068
R4: 30k; R_0603_1608Metric; LCSC Part # C2907025
R5: 220k; R_0603_1608Metric; LCSC Part # C22961
R6: 100k; R_0603_1608Metric; LCSC Part # C25803
U1: LMR51606YDBVR; SOT-23-6; LCSC Part # C33545953
U2: TPS2553DBVR; SOT-23-6; LCSC Part # C55266

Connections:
5V: C4.1, C5.1, C6.1, L1.2, R3.1, R6.2, U2.1 (IN), U2.3 (EN)
/CB: C3.1, U1.1 (CB)
/DM: J2.2 (D-), JP1.1 (A)
/DP: J2.3 (D+), JP1.2 (B)
/EN: R1.2, R2.1, U1.4 (EN)
/FB: R3.2, R4.1, U1.3 (FB)
/FLT: R6.1, U2.4 (~FAULT)
/ILIM: R5.1, U2.5 (ILIM)
/SW: C3.2, L1.1, U1.6 (SW)
/VBUS: C7.1, C8.1, J2.1 (VBUS), U2.6 (OUT)
/VIN: C1.1, C2.1, D2.1 (K), R1.1, U1.5 (VIN)
/VIN_RAW: D1.1 (K), D2.2 (A), J1.1
GND: C1.2, C2.2, C4.2, C5.2, C6.2, C7.2, C8.2, D1.2 (A), J1.2, J2.4 (GND), J2.SH (Shield), R2.2, R4.2, R5.2, U1.2 (GND), U2.2 (GND)

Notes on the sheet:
UVLO divider R1/R2: on at ~9.0 V, off at ~7.3 V. Feedback R3/R4 (118k / 22.1k): 5.07 V out.
USB OUTPUT (TPS2553 current-limited switch, ~117 mA)
From the ESP32 board's J2 (TAB_OUT, ~16 V, current-limited to ~87 mA there by limiter 2). D1 SMBJ24A sits before D2: if the cable is wired backwards D1 conducts, limiter 2 holds the current and the firmware switches the output off. D2 SS16 blocks reverse current.
INPUT PROTECTION
5 V BUCK (LMR51606, 1.1 MHz PFM)
R5 232k sets the limit to ~117 mA typ. The TPS2553 (not the -1 version) holds a constant current in overload rather than latching off, so a tablet asking for 1-2 A just sees VBUS sag. JP1 open (default): D+/D- left open, a basic USB port. Close JP1 to short D+/D- ("dedicated charger") if the tablet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

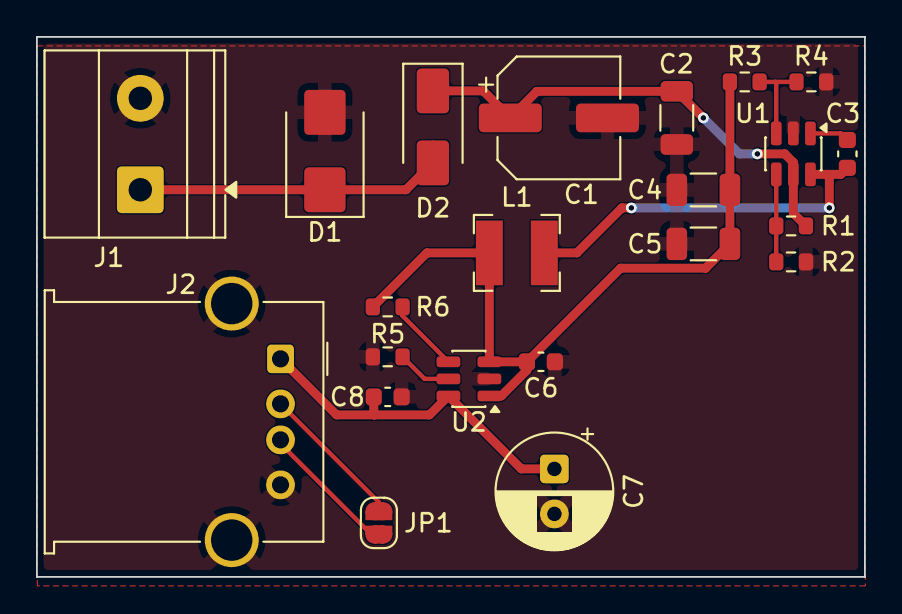
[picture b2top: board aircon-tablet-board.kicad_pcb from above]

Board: 2 copper layers, 46.0 x 30.0 mm, 22 parts (0 on the bottom side), 13 nets.

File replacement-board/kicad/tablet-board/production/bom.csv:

Designator,Footprint,Quantity,Value,LCSC Part #
C1,CP_Elec_6.3x7.7,1,100uF 35V,C2992597
C2,1206,1,2.2uF 50V X7R,C50254
"C3, C6, C8",0603,3,100nF,C1591
"C4, C5",1206,2,10uF 50V X5R,C13585
C7,CP_Radial_D6.3mm_P2.50mm,1,100uF 16 V,C55265386
D1,D_SMB,1,SMBJ24A,C5178956
D2,D_SMA,1,SS16,C2481
J1,"TerminalBlock_Phoenix_MKDS-1,5-2-5.08_1x02_P5.08mm_Horizontal",1,From ESP32 board,C474952
J2,USB_A_Molex_67643_Horizontal,1,USB-A receptacle,C293351
L1,L_Bourns-SRN4018,1,10uH >=0.6A,C503307
R1,0603,1,1M,C22935
R2,0603,1,150k,C22807
R3,0603,1,160k,C2930068
R4,0603,1,30k,C2907025
R5,0603,1,220k,C22961
R6,0603,1,100k,C25803
U1,SOT-23-6,1,LMR51606YDBVR,C33545953
U2,SOT-23-6,1,TPS2553DBVR,C55266

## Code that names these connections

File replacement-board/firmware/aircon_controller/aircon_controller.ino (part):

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const char* HOSTNAME = "aircon";
const char* MODEL    = "Leasam B512W3 replacement";
constexpr int PIN_TX     = 4;          // -> R_G -> C_G -> Q_TX gate. High = pull POWER low.
constexpr int PIN_VRES   = 3;          // VSENSE: VRES via 150k / 10k
constexpr int PIN_AUX    = 0;          // AUX via 330k / 100k, 10 nF
constexpr int PIN_VTAB   = 1;          // tablet output via 150k / 10k
constexpr int PIN_TAB_EN = 5;          // high = tablet output on (via Q_EN)
constexpr int PIN_LED    = 10;         // on while MQTT is connected
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const char* HOSTNAME = "aircon-test";
const char* MODEL    = "Leasam B512W3 replacement (breadboard)";
constexpr int PIN_TX   = 25;           // -> C1 -> R1 -> Q1 base. High = pull POWER low.
constexpr int PIN_AUX  = 34;           // AUX via 100k / 33k (ADC1, input only)
constexpr int PIN_VRES = 35;           // VRES via R9 100k / R10 10k (ADC1, input only; stage 2)
constexpr int PIN_LED  = 2;            // on-board LED on most DevKits: on while MQTT is connected
// Calibrated against a meter on the AUX node (4.27 V on the meter, 4.33 V reported, same moment).
// Covers the 10k + 20k + 3k chain standing in for the 33k, and the ADC's own error.
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constexpr uint32_t ROOMS_SETTLE_MS = 1000;   // room changes come in bursts

// ---------- tablet output (PCB) ----------
constexpr float    TAB_ON_MIN_V      = 14.0f;   // VRES must be at least this to switch on...
constexpr uint32_t TAB_ON_SETTLE_MS  = 10000;   // ...continuously for this long
constexpr float    TAB_SHED_V        = 13.0f;   // VRES below this -> switch off (protect the ESP32)
constexpr uint32_t TAB_SHED_MS       = 500;
constexpr float    TAB_FAULT_V       = 10.0f;   // output below this while on -> short/overload
constexpr uint32_t TAB_FAULT_MS      = 2000;
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constexpr uint32_t WIFI_START_TIMEOUT_MS = 20000;

// ---------- reporting ----------
constexpr uint32_t AUX_PUBLISH_MS  = 10000;   // AUX and VRES: mean, min and max over this period
constexpr uint32_t RSSI_PUBLISH_MS = 30000;
constexpr uint32_t MQTT_RETRY_MS   = 5000;
constexpr uint32_t UPTIME_PUBLISH_MS = 60000;
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    Window b;
    b.reset();
    for (int i = 0; i < 10; i++) {
      float a = readVolts(PIN_AUX, AUX_RATIO);
      float v = readVolts(PIN_VRES, VRES_RATIO);
      b.auxSum += a; b.auxMin = min(b.auxMin, a); b.auxMax = max(b.auxMax, a);
      b.vresSum += v; b.vresMin = min(b.vresMin, v);
#if BOARD_PCB
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#endif
  pinMode(PIN_LED, OUTPUT);
  digitalWrite(PIN_LED, LOW);
  analogSetPinAttenuation(PIN_AUX, ADC_11db);
  analogSetPinAttenuation(PIN_VRES, ADC_11db);

  prefs.begin("aircon", false);
  powerOn = false;                     // always start off, whatever was set before the reboot
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
#if BOARD_PCB
  // Let the reservoir charge before Wi-Fi's current bursts.
  vresAtBoot = readVolts(PIN_VRES, VRES_RATIO);
  uint32_t t0 = millis();
  while (readVolts(PIN_VRES, VRES_RATIO) < WIFI_START_MIN_V && millis() - t0 < WIFI_START_TIMEOUT_MS) delay(100);
  wifiWaitMs = millis() - t0;
#endif

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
